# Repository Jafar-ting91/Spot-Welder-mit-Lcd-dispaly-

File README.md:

# STM32 Capacitor Spot Welder with TFT Display

DIY capacitor spot welder based on STM32 with TFT display, adjustable welding pulses, configurable charging control and safety features.

## Overview

This project is a self-built capacitor spot welder based on an STM32 microcontroller.  
It is designed for controlled battery tab welding with adjustable pulse settings, TFT user interface, voltage monitoring and configurable protection features.

### Proven in real use

- **Version 1:** over **100,000 weld points**
- **Current version:** over **30,000 weld points**

This is not just a prototype – the device has already been used extensively in practical operation.

## Main Features

- STM32-based control
- TFT display with menu interface
- Adjustable welding pulses
- Configurable pulse / pause / pulse timing
- Voltage monitoring
- Temperature monitoring
- Adjustable charge control
- Safety limits and warning thresholds
- Rotary encoder based user input

## User Interface

## Bilder / Images

### Fertiges Punktschweißgerät

### Bedienoberfläche

### Einstellungen

### Elektronik

### Weitere Ansicht

## Project Status

**Active development**  
The spot welder is functional and used regularly in real-world applications.

## Notes

This project is intended for users with experience in electronics and high-current systems.  
Working with capacitor discharge systems and battery welding can be dangerous if handled improperly.

## License

Apache-2.0

---

# Deutsch

## Übersicht

Dies ist ein selbstgebautes Punktschweißgerät auf STM32-Basis mit TFT-Display.  
Es ist für kontrolliertes Akkuschweißen ausgelegt und bietet einstellbare Schweißpulse, Spannungsüberwachung, Temperaturüberwachung sowie verschiedene Schutzfunktionen.

### In der Praxis bewährt

- **Version 1:** über **100.000 Schweißpunkte**
- **Aktuelle Version:** über **30.000 Schweißpunkte**

Das Projekt ist also nicht nur ein Prototyp, sondern wurde bereits intensiv praktisch eingesetzt.

## Hauptfunktionen

- STM32-basierte Steuerung
- TFT-Display mit Menüoberfläche
- Einstellbare Schweißpulse
- Konfigurierbare Puls-/Pausenzeiten
- Spannungsüberwachung
- Temperaturüberwachung
- Einstellbare Ladeparameter
- Schutz- und Warnschwellen
- Bedienung per Drehencoder

## Projektstatus

**Aktiv in Entwicklung**  
Das Gerät ist funktionsfähig und wird regelmäßig im praktischen Einsatz verwendet.

## 💖 Support this project

If you like this project and want to support its development:

👉 https://paypal.me/Zaharg

Thank you! 🙏

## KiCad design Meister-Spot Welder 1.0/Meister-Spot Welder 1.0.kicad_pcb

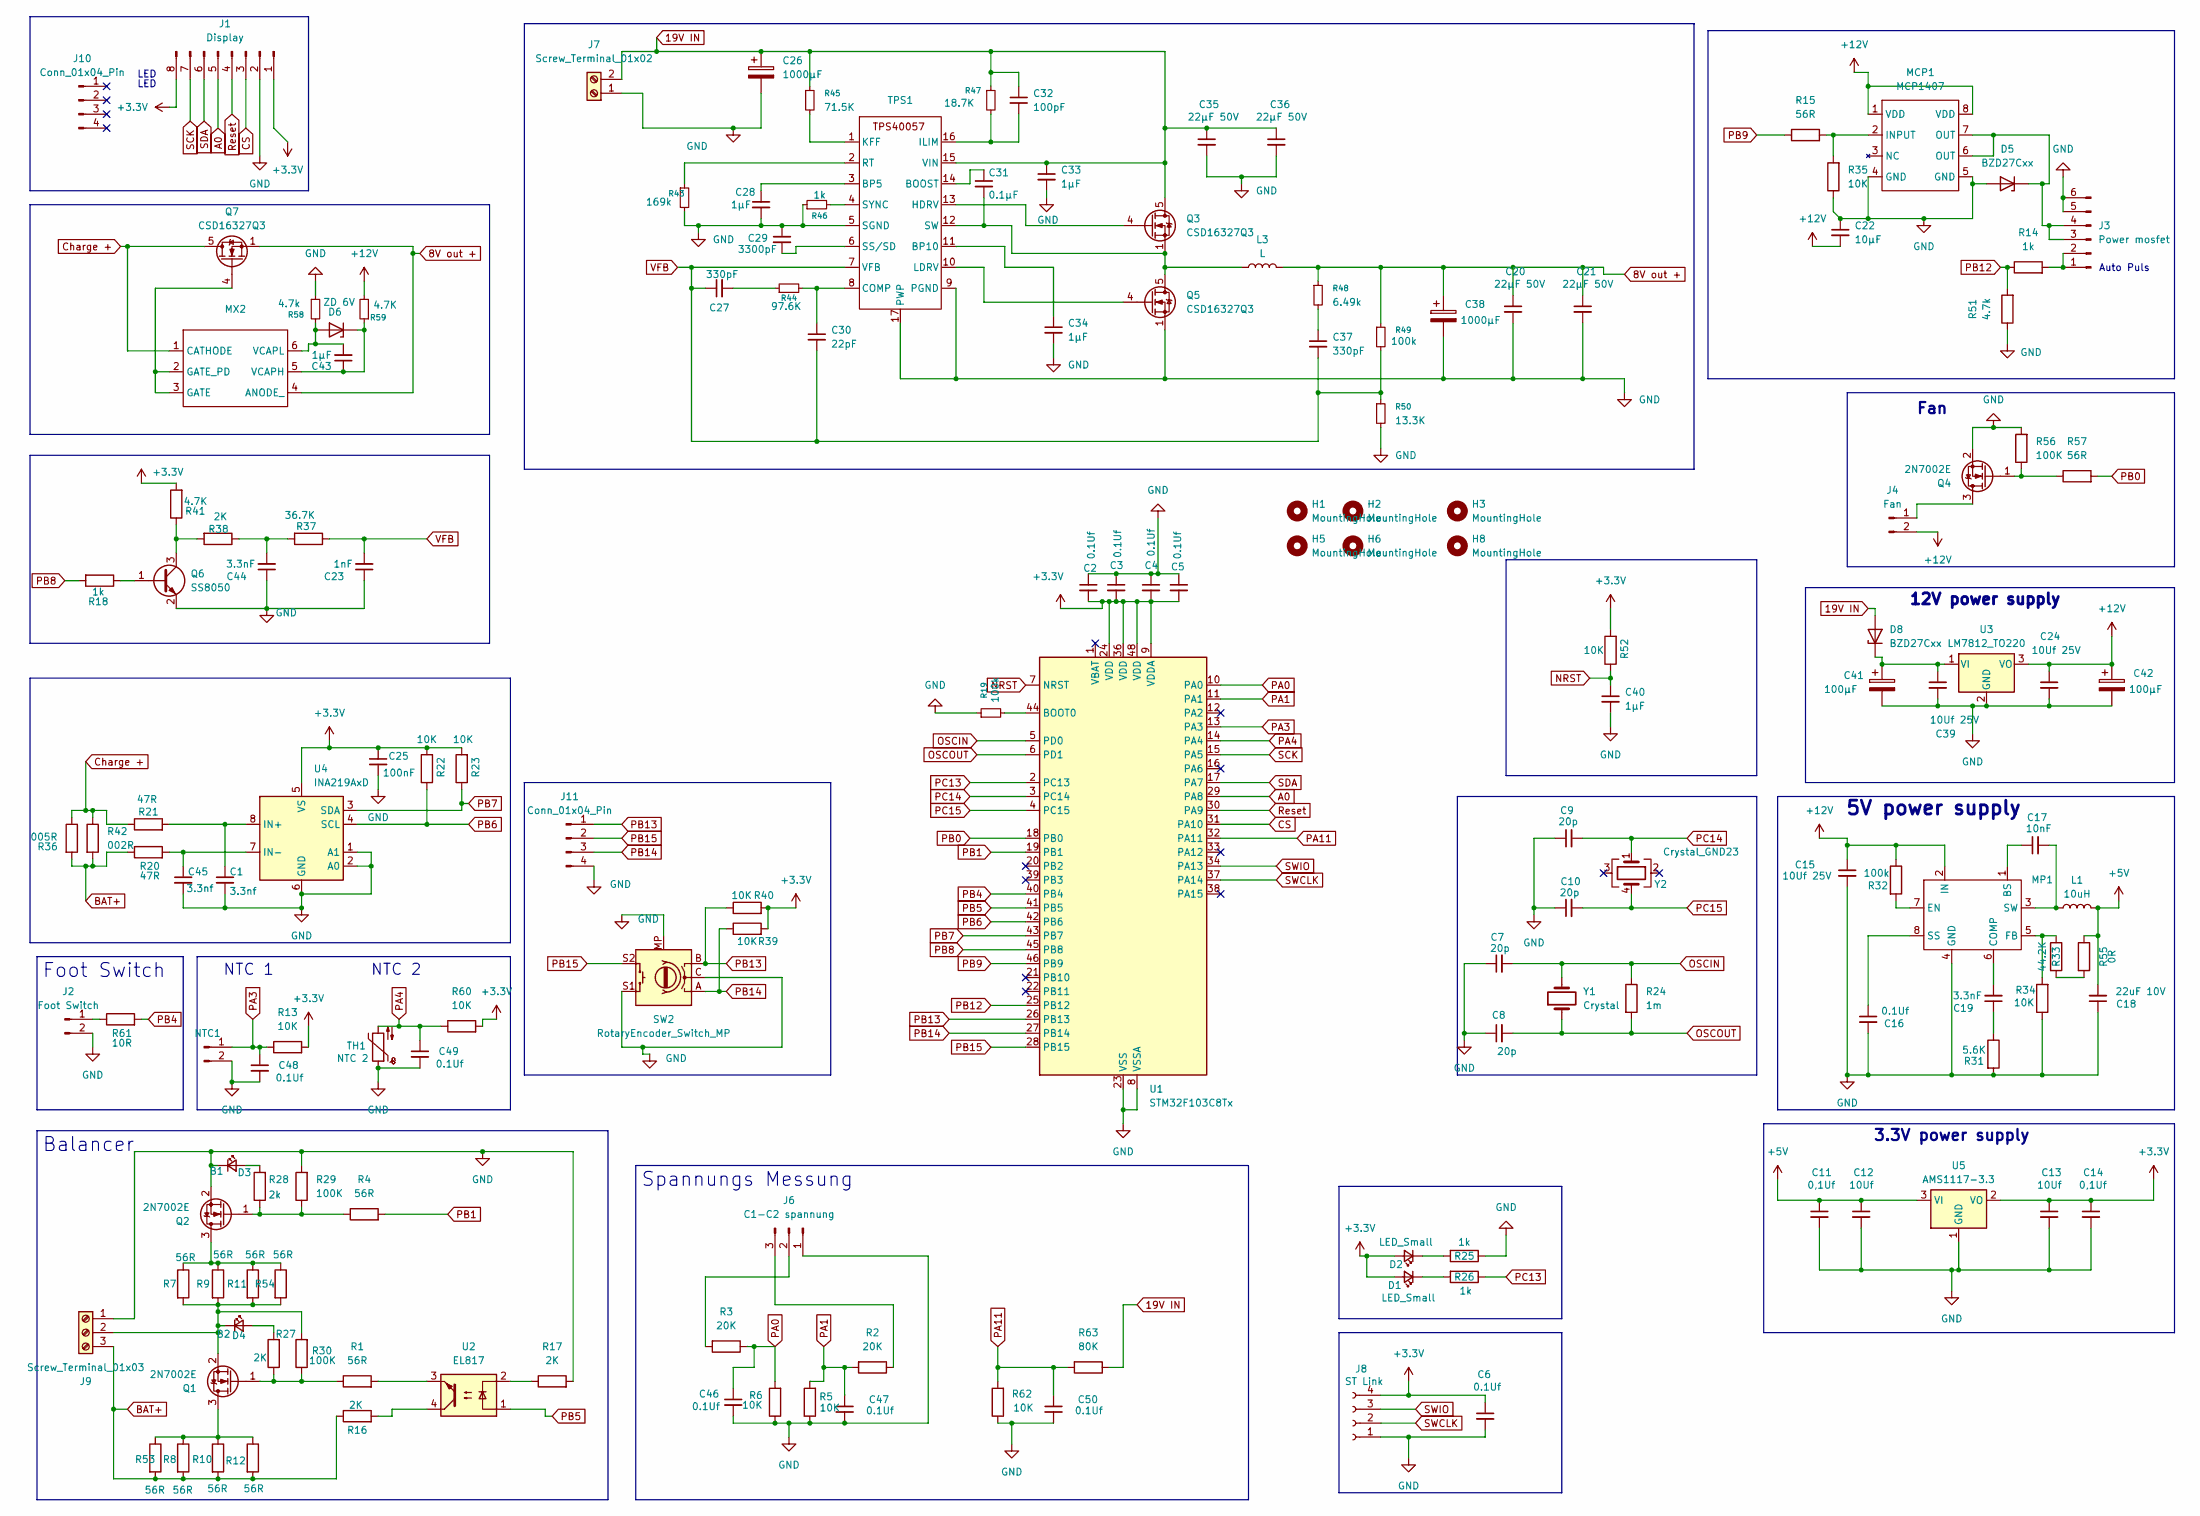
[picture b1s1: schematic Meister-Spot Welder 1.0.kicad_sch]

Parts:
C1, C45: 3.3nf; C_0603_1608Metric_Pad1.08x0.95mm_HandSolder
C2, C3, C4, C5, C6, C16, C46, C47, C48, C49, C50: 0.1Uf; C_0603_1608Metric_Pad1.08x0.95mm_HandSolder
C7, C8, C9, C10: 20p; C_0603_1608Metric_Pad1.08x0.95mm_HandSolder
C11, C14: 0,1Uf; C_0603_1608Metric_Pad1.08x0.95mm_HandSolder
C12, C13: 10Uf; C_0805_2012Metric
C15, C24, C39: 10Uf 25V; C_1206_3216Metric_Pad1.33x1.80mm_HandSolder
C17: 10nF; C_0603_1608Metric_Pad1.08x0.95mm_HandSolder
C18: 22uF 10V; C_1206_3216Metric_Pad1.33x1.80mm_HandSolder
C19, C44: 3.3nF; C_0603_1608Metric_Pad1.08x0.95mm_HandSolder
C20, C21, C35, C36: 22µF 50V; C_1206_3216Metric_Pad1.33x1.80mm_HandSolder
C22: 10µF; C_0805_2012Metric
C23: 1nF; C_0603_1608Metric_Pad1.08x0.95mm_HandSolder
C25: 100nF; C_0603_1608Metric_Pad1.08x0.95mm_HandSolder
C26, C38: 1000µF; CP_Radial_D10.0mm_P5.00mm
C27, C37: 330pF; C_0603_1608Metric_Pad1.08x0.95mm_HandSolder
C28, C33, C34, C40, C43: 1µF; C_0603_1608Metric_Pad1.08x0.95mm_HandSolder
C29: 3300pF; C_0603_1608Metric_Pad1.08x0.95mm_HandSolder
C30: 22pF; C_0603_1608Metric_Pad1.08x0.95mm_HandSolder
C31: 0.1µF; C_0603_1608Metric_Pad1.08x0.95mm_HandSolder
C32: 100pF; C_0603_1608Metric_Pad1.08x0.95mm_HandSolder
C41, C42: 100µF; CP_Elec_6.3x5.9
D1, D2: LED_Small; LED_0603_1608Metric_Pad1.05x0.95mm_HandSolder
D3: B1; LED_0603_1608Metric_Pad1.05x0.95mm_HandSolder
D4: B2; LED_0603_1608Metric_Pad1.05x0.95mm_HandSolder
D5: BZD27Cxx; D_SMF
D6: ZD 6V; D_SMF
D8: BZD27Cxx; D_SOD-128
H1, H2, H3, H5, H6, H8: MountingHole; MountingHole_3.2mm_M3
J1: Display; PinHeader_1x08_P2.54mm_Vertical
J2: Foot Switch; JST_EH_B2B-EH-A_1x02_P2.50mm_Vertical
J3: Power mosfet; PinHeader_1x06_P2.54mm_Vertical
J4: Fan; JST_EH_B2B-EH-A_1x02_P2.50mm_Vertical
J5: NTC1; JST_EH_B2B-EH-A_1x02_P2.50mm_Vertical
J6: C1-C2 spannung; JST_EH_B3B-EH-A_1x03_P2.50mm_Vertical
J7: Screw_Terminal_01x02; PhoenixContact_MCV_1,5_2-G-5.08_1x02_P5.08mm_Vertical
J8: ST Link; PinHeader_1x04_P2.54mm_Vertical
J9: Screw_Terminal_01x03; PhoenixContact_MCV_1,5_3-G-5.08_1x03_P5.08mm_Vertical
J10, J11: Conn_01x04_Pin; PinHeader_1x04_P2.54mm_Vertical
L1: 10uH; L_7.3x7.3_H3.5
L3: L; L_Toroid_Vertical_L17.8mm_W9.7mm_P7.11mm_Pulse_B
MCP1: MCP1407; SOIC-8_3.9x4.9mm_P1.27mm
MP1: SO-8_3.9x4.9mm_P1.27mm
MX2: SOT-23-6
Q1, Q2, Q4: 2N7002E; SOT-23-3
Q3, Q5, Q7: CSD16327Q3; PowerPAK_SO-8_Single
Q6: SS8050; SOT-23
R1, R4, R15, R57: 56R; R_0603_1608Metric_Pad0.98x0.95mm_HandSolder
R2, R3: 20K; R_0603_1608Metric_Pad0.98x0.95mm_HandSolder
R5, R6, R13, R22, R23, R34, R35, R39, R40, R52, R60, R62: 10K; R_0603_1608Metric_Pad0.98x0.95mm_HandSolder
R7, R8, R9, R10, R11, R12, R53, R54: 56R; R_2010_5025Metric_Pad1.40x2.65mm_HandSolder
R14, R18, R25, R26, R46: 1k; R_0603_1608Metric_Pad0.98x0.95mm_HandSolder
R16, R17, R27, R38: 2K; R_0603_1608Metric_Pad0.98x0.95mm_HandSolder
R19, R32, R49: 100k; R_0603_1608Metric_Pad0.98x0.95mm_HandSolder
R20, R21: 47R; R_0603_1608Metric_Pad0.98x0.95mm_HandSolder
R24: 1m; R_0603_1608Metric_Pad0.98x0.95mm_HandSolder
R28: 2k; R_0603_1608Metric_Pad0.98x0.95mm_HandSolder
R29, R30, R56: 100K; R_0603_1608Metric_Pad0.98x0.95mm_HandSolder
R31: 5.6K; R_0603_1608Metric_Pad0.98x0.95mm_HandSolder
R33: 44.2K; R_0603_1608Metric_Pad0.98x0.95mm_HandSolder
R36: 005R; R_2512_6332Metric
R37: 36.7K; R_0603_1608Metric_Pad0.98x0.95mm_HandSolder
R41, R59: 4.7K; R_0603_1608Metric_Pad0.98x0.95mm_HandSolder
R42: 002R; R_2512_6332Metric
R43: 169k; R_0603_1608Metric_Pad0.98x0.95mm_HandSolder
R44: 97.6K; R_0603_1608Metric_Pad0.98x0.95mm_HandSolder
R45: 71.5K; R_0603_1608Metric_Pad0.98x0.95mm_HandSolder
R47: 18.7K; R_0603_1608Metric_Pad0.98x0.95mm_HandSolder
R48: 6.49k; R_0603_1608Metric_Pad0.98x0.95mm_HandSolder
R50: 13.3K; R_0603_1608Metric_Pad0.98x0.95mm_HandSolder
R51, R58: 4.7k; R_0603_1608Metric_Pad0.98x0.95mm_HandSolder
R55: 0R; R_0603_1608Metric_Pad0.98x0.95mm_HandSolder
R61: 10R; R_0603_1608Metric_Pad0.98x0.95mm_HandSolder
R63: 80K; R_0603_1608Metric_Pad0.98x0.95mm_HandSolder
SW2: RotaryEncoder_Switch_MP; RotaryEncoder_Alps_EC11E-Switch_Vertical_H20mm
TH1: NTC 2; R_0603_1608Metric
TPS1: HTSSOP-16-1EP_4.4x5mm_P0.65mm_EP3x3mm
U1: STM32F103C8Tx; LQFP-48_7x7mm_P0.5mm
U2: EL817; DIP-4_W7.62mm
U3: LM7812_TO220; TO-252-2
U4: INA219AxD; SOIC-8_3.9x4.9mm_P1.27mm
U5: AMS1117-3.3; SOT-223-3_TabPin2
Y1: Crystal; Crystal_HC49-4H_Vertical
Y2: Crystal_GND23; Crystal_SMD_SeikoEpson_MC306-4Pin_8.0x3.2mm

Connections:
8V out +: C20.1, C21.1, C38.1, L3.2, MX2.4 (ANODE_), Q7.1 (S), Q7.2 (S), Q7.3 (S), R48.1, R49.1
19V IN: C26.1, C32.1, C33.1, C35.1, C36.1, D8.2 (A), J7.2, Q3.5 (D), R45.1, R47.1, R63.1, TPS1.15 (VIN)
+3.3V: C2.2, C3.2, C4.2, C5.2, C6.1, C13.1, C14.1, C25.1, D1.2 (A), D2.2 (A), J1.1, J1.8, J8.4, R13.2, R22.2, R23.2, R39.2, R40.2, R41.2, R52.2, R60.2, U1.9 (VDDA), U1.24 (VDD), U1.36 (VDD), U1.48 (VDD), U4.5 (VS), U5.2 (VO)
+5V: C11.1, C12.1, C18.2, L1.2, R55.1, U5.3 (VI)
+12V: C15.1, C22.2, C24.1, C42.1, J4.2, MCP1.1 (VDD), MCP1.8 (VDD), MP1.2 (IN), R32.1, R59.2, U3.3 (VO)
A0: J1.5, U1.29 (PA8)
BAT+: J9.3, R8.2, R10.2, R12.2, R16.1, R20.1, R36.2, R42.2, R53.2
CS: J1.3, U1.31 (PA10)
Charge +: MX2.1 (CATHODE), Q7.5 (D), R21.1, R36.1, R42.1
GND: C1.2, C2.1, C3.1, C4.1, C5.1, C6.2, C7.1, C8.1, C9.1, C10.1, C11.2, C12.2, C13.2, C14.2, C15.2, C16.2, C18.1, C20.2, C21.2, C22.1, C23.1, C24.2, C25.2, C26.2, C28.2, C29.1, C33.2, C34.2, C35.2, C36.2, C38.2, C39.2, C40.2, C41.2, C42.2, C44.1, C45.2, C46.2, C47.2, C48.2, C49.2, C50.2, D3.1 (K), D5.2 (A), J1.2, J2.2, J3.5, J3.6, J5.2, J6.1, J7.1, J8.1, J9.1, J11.4, MCP1.4 (GND), MCP1.5 (GND), MP1.4 (GND), Q2.2 (S), Q4.2 (S), Q5.1 (S), Q5.2 (S), Q5.3 (S), Q6.2 (E), R5.1, R6.1, R17.2, R19.1, R25.1, R29.2, R31.2, R34.1, R35.1, R43.2, R46.1, R50.2, R51.1, R56.2, R58.1, R62.1, SW2.C, SW2.MP, SW2.S1, TH1.1, TPS1.5 (SGND), TPS1.9 (PGND), TPS1.17 (PWP), U1.8 (VSSA), U1.23 (VSS), U1.35 (VSS), U1.47 (VSS), U3.2 (GND), U4.1 (A1), U4.2 (A0), U4.6 (GND), U5.1 (GND)
NRST: C40.1, R52.1, U1.7 (NRST)
unnamed: C19.1, R31.1
unnamed: C27.2, R44.1
unnamed: C37.1, R48.2
unnamed: C44.2, R37.2, R38.1
unnamed: D1.1 (K), R26.2
unnamed: D2.1 (K), R25.2
unnamed: D3.2 (A), R28.2
unnamed: D4.2 (A), R27.2
unnamed: D4.1 (K), J9.2, Q1.2 (S), R7.2, R9.2, R11.2, R30.2, R54.2
unnamed: D5.1 (K), J3.3, J3.4, MCP1.6 (OUT), MCP1.7 (OUT)
unnamed: C43.2, D6.2 (A), MX2.6 (VCAPL), R58.2
unnamed: C43.1, D6.1 (K), MX2.5 (VCAPH), R59.1
unnamed: C39.1, C41.1, D8.1 (K), U3.1 (VI)
unnamed: J2.1, R61.1
unnamed: J3.1, J3.2, R14.2
unnamed: J4.1, Q4.3 (D)
unnamed: J6.2, R3.2
unnamed: J6.3, R2.1
unnamed: MCP1.2 (INPUT), R15.2, R35.2
unnamed: C17.1, MP1.1 (BS)
unnamed: C19.2, MP1.6 (COMP)
unnamed: MP1.7 (EN), R32.2
unnamed: MP1.5 (FB), R33.1, R34.2
unnamed: C16.1, MP1.8 (SS)
unnamed: C17.2, L1.1, MP1.3 (SW)
unnamed: MX2.2 (GATE_PD), MX2.3 (GATE), Q7.4 (G)
unnamed: Q1.3 (D), R8.1, R10.1, R12.1, R53.1
unnamed: Q1.1 (G), R1.1, R27.1, R30.1
unnamed: Q2.3 (D), R7.1, R9.1, R11.1, R54.1
unnamed: Q2.1 (G), R4.1, R28.1, R29.1
unnamed: Q3.4 (G), TPS1.13 (HDRV)
unnamed: Q4.1 (G), R56.1, R57.1
unnamed: C31.2, L3.1, Q3.1 (S), Q3.2 (S), Q3.3 (S), Q5.5 (D), TPS1.12 (SW)
unnamed: Q5.4 (G), TPS1.10 (LDRV)
unnamed: Q6.1 (B), R18.1
unnamed: Q6.3 (C), R38.2, R41.1
unnamed: R1.2, U2.3
unnamed: R16.2, U2.4
unnamed: R17.1, U2.2
unnamed: R33.2, R55.2
unnamed: C31.1, TPS1.14 (BOOST)
unnamed: C28.1, TPS1.3 (BP5)
unnamed: C34.1, TPS1.11 (BP10)
unnamed: C30.1, R44.2, TPS1.8 (COMP)
unnamed: C32.2, R47.2, TPS1.16 (ILIM)
unnamed: R45.2, TPS1.1 (KFF)
unnamed: R43.1, TPS1.2 (RT)
unnamed: C29.2, TPS1.6 (SS/SD)
unnamed: R46.2, TPS1.4 (SYNC)
unnamed: R19.2, U1.44 (BOOT0)
unnamed: C1.1, R21.2, U4.8 (IN+)
unnamed: C45.1, R20.2, U4.7 (IN-)
OSCIN: C7.2, R24.1, U1.5 (PD0), Y1.2
OSCOUT: C8.2, R24.2, U1.6 (PD1), Y1.1
PA0: C46.1, R3.1, R6.2, U1.10 (PA0)
PA1: C47.1, R2.2, R5.2, U1.11 (PA1)
PA3: C48.1, J5.1, R13.1, U1.13 (PA3)
PA4: C49.1, R60.1, TH1.2, U1.14 (PA4)
PA11: C50.1, R62.2, R63.2, U1.32 (PA11)
PB0: R57.2, U1.18 (PB0)
PB1: R4.2, U1.19 (PB1)
PB4: R61.2, U1.40 (PB4)
PB5: U1.41 (PB5), U2.1
PB6: R22.1, U1.42 (PB6), U4.4 (SCL)
PB7: R23.1, U1.43 (PB7), U4.3 (SDA)
PB8: R18.2, U1.45 (PB8)
PB9: R15.1, U1.46 (PB9)
PB12: R14.1, R51.2, U1.25 (PB12)
PB13: J11.1, R40.1, SW2.B, U1.26 (PB13)
PB14: J11.3, R39.1, SW2.A, U1.27 (PB14)
PB15: J11.2, SW2.S2, U1.28 (PB15)
PC13: R26.1, U1.2 (PC13)
PC14: C9.2, U1.3 (PC14), Y2.1
PC15: C10.2, U1.4 (PC15), Y2.4
Reset: J1.4, U1.30 (PA9)
SCK: J1.7, U1.15 (PA5)
SDA: J1.6, U1.17 (PA7)
SWCLK: J8.2, U1.37 (PA14)
SWIO: J8.3, U1.34 (PA13)
VFB: C23.2, C27.1, C30.2, C37.2, R37.1, R49.2, R50.1, TPS1.7 (VFB)

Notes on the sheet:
3.3V power supply
LED
NTC 1
NTC 2
Auto Puls
12V power supply
5V power supply
Fan
Foot Switch
Balancer
Spannungs Messung

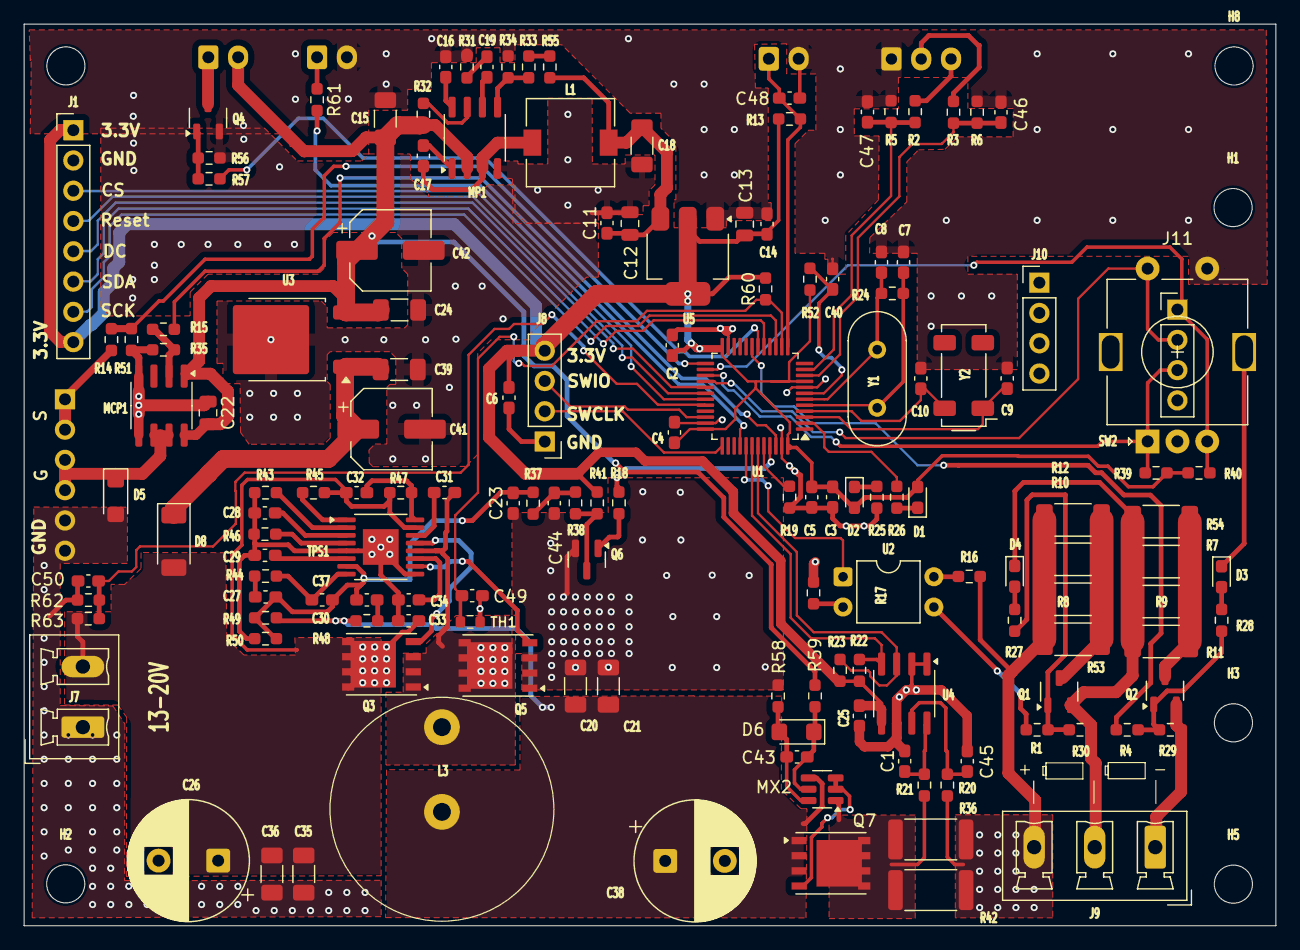
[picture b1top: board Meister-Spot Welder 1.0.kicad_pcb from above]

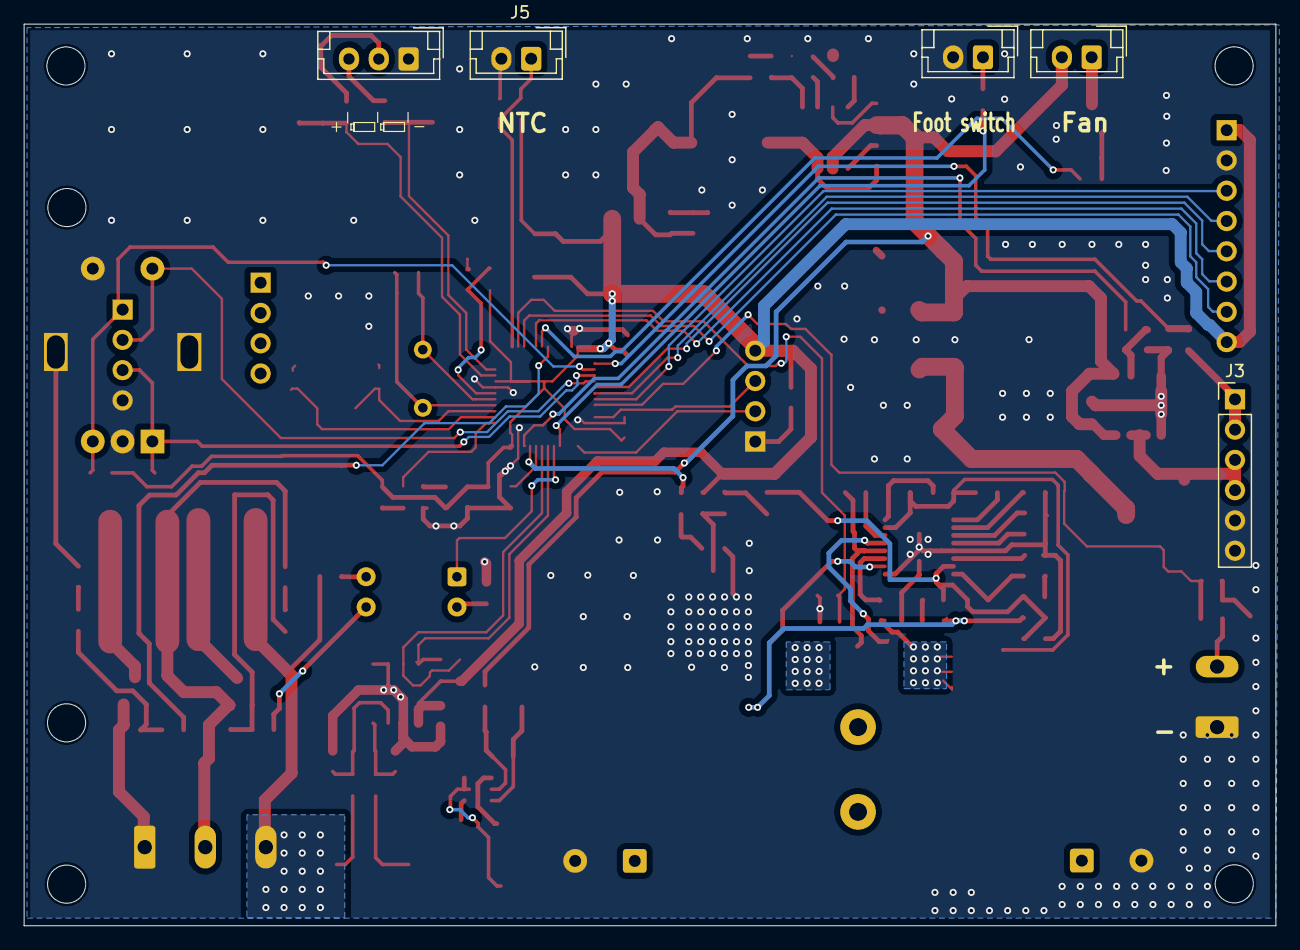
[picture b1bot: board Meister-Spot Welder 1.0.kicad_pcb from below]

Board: 2 copper layers, 105.0 x 75.6 mm, 159 parts (5 on the bottom side), 91 nets.

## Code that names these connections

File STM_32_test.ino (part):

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#endif

// =================== Hardware / Pins ===================
#define MOSFET_PIN     PB8
#define TFT_CS         PA10
#define TFT_RST        PA9
#define TFT_DC         PA8
#define ENCODER_A      PB13
#define ENCODER_B      PB14
#define ENCODER_BTN    PB15
#define START_BTN      PB4
#define CAP1_PIN       PA0
#define CAP2_PIN       PA1
#define PULSE_PIN      PB9
#define TEMP_PIN       PA3
#define TEMP2_PIN      PA4
#define AUTO_PULSE_PIN PB12
#define BALANCE_C1_PIN PB1
#define BALANCE_C2_PIN PB5
#define FAN_PIN        PB0

// =================== Farben ===================
#define ST77XX_BLACK   ILI9341_BLACK
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    wasCharging = false;
  }

  // ======= TRIGGER: PB4 & PB12 =======
  {
    static uint8_t lastPB4  = HIGH;
    static uint8_t lastPB12 = LOW;
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
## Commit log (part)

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2026-04-04 Update README.md
    ⚠️ Projektstatus
    🟡 Aktiv in Entwicklung
    Die aktuelle Version ist voll funktionsfähig und wird im praktischen Einsatz verwendet.
    Alle Hauptfunktionen (Laden, Schweißen, Anzeige, Schutzmechanismen) laufen stabil.
    👉 Trotzdem gilt:
    Einige Bereiche sind noch in Optimierung
